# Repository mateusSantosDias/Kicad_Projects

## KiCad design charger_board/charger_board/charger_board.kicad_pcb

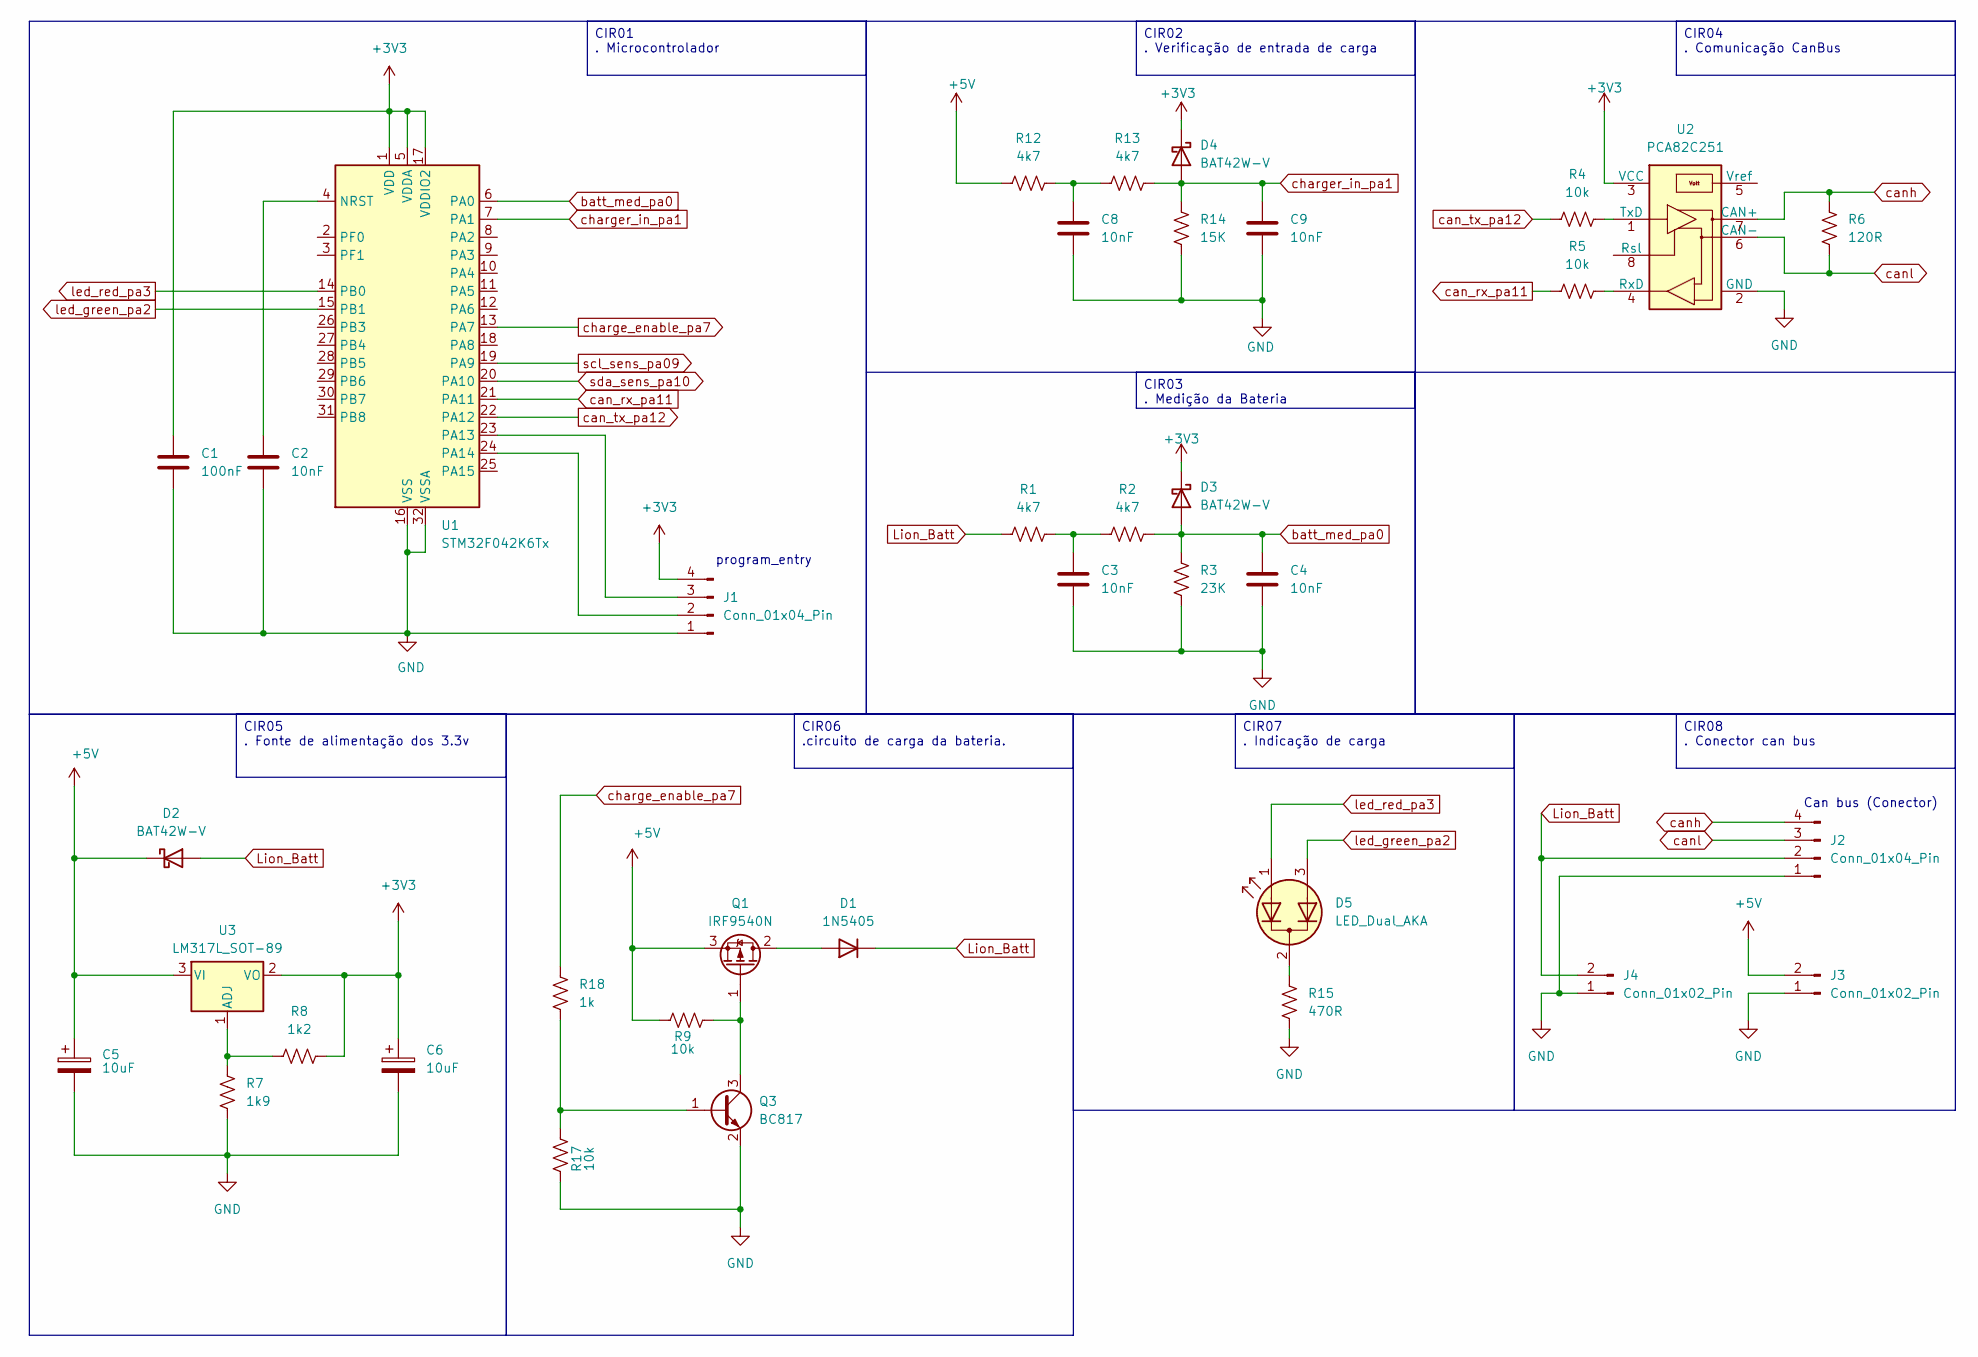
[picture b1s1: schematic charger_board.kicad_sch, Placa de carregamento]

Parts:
C1: 100nF; C_1206_3216Metric
C2, C3, C4, C8, C9: 10nF; C_1206_3216Metric
C5, C6: 10uF; C_Elec_5x5.4
D1: 1N5405; D_1206_3216Metric
D2, D3, D4: BAT42W-V; D_SOD-123
D5: LED_Dual_AKA; LED_D3.0mm-3
J1, J2: Conn_01x04_Pin; PinHeader_1x04_P2.54mm_Vertical
J3, J4: Conn_01x02_Pin; PinHeader_1x02_P2.54mm_Vertical
Q1: IRF9540N; TO-252-2
Q3: BC817; SOT-23
R1, R2, R12, R13: 4k7; R_1206_3216Metric
R3: 23K; R_1206_3216Metric
R4, R5, R9, R17: 10k; R_1206_3216Metric
R6: 120R; R_1206_3216Metric
R7: 1k9; R_1206_3216Metric
R8: 1k2; R_1206_3216Metric
R14: 15K; R_1206_3216Metric
R15: 470R; R_1206_3216Metric
R18: 1k; R_1206_3216Metric
U1: STM32F042K6Tx; LQFP-32_7x7mm_P0.8mm
U2: PCA82C251; SO-8_3.9x4.9mm_P1.27mm
U3: LM317L_SOT-89; SOT-89-3

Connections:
+3V3: C1.1, C6.1, D3.1 (K), D4.1 (K), J1.4, R8.2, U1.1 (VDD), U1.5 (VDDA), U1.17 (VDDIO2), U2.3 (VCC), U3.2 (VO)
+5V: C5.1, D2.1 (K), J3.2, Q1.3 (S), R9.2, R12.1, U3.3 (VI)
GND: C1.2, C2.2, C3.2, C4.2, C5.2, C6.2, C8.2, C9.2, J1.1, J2.1, J3.1, J4.1, Q3.2 (E), R3.1, R7.1, R14.1, R15.1, R17.2, U1.16 (VSS), U1.32 (VSSA), U2.2 (GND)
Lion_Batt: D1.1 (K), D2.2 (A), J2.2, J4.2, R1.1
unnamed: C3.1, R1.2, R2.1
unnamed: C8.1, R12.2, R13.1
unnamed: D1.2 (A), Q1.2 (D)
unnamed: D5.2 (K), R15.2
unnamed: J1.2, U1.24 (PA14)
unnamed: J1.3, U1.23 (PA13)
unnamed: Q1.1 (G), Q3.3 (C), R9.1
unnamed: Q3.1 (B), R17.1, R18.2
unnamed: C2.1, U1.4 (NRST)
unnamed: R5.2, U2.4 (RxD)
unnamed: R4.2, U2.1 (TxD)
unnamed: R7.2, R8.1, U3.1 (ADJ)
batt_med_pa0: C4.1, D3.2 (A), R2.2, R3.2, U1.6 (PA0)
can_rx_pa11: R5.1, U1.21 (PA11)
can_tx_pa12: R4.1, U1.22 (PA12)
canh: J2.4, R6.2, U2.7 (CAN+)
canl: J2.3, R6.1, U2.6 (CAN-)
charge_enable_pa7: R18.1, U1.13 (PA7)
charger_in_pa1: C9.1, D4.2 (A), R13.2, R14.2, U1.7 (PA1)
led_green_pa2: D5.3 (A2), U1.15 (PB1)
led_red_pa3: D5.1 (A1), U1.14 (PB0)
scl_sens_pa09: U1.19 (PA9)
sda_sens_pa10: U1.20 (PA10)

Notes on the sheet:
Can bus (Conector)
program_entry
CIR06 .circuito de carga da bateria.
CIR07 . Indicação de carga
CIR08 . Conector can bus
CIR05 . Fonte de alimentação dos 3.3v
CIR04 . Comunicação CanBus
CIR02 . Verificação de entrada de carga
CIR01 . Microcontrolador
CIR03 . Medição da Bateria

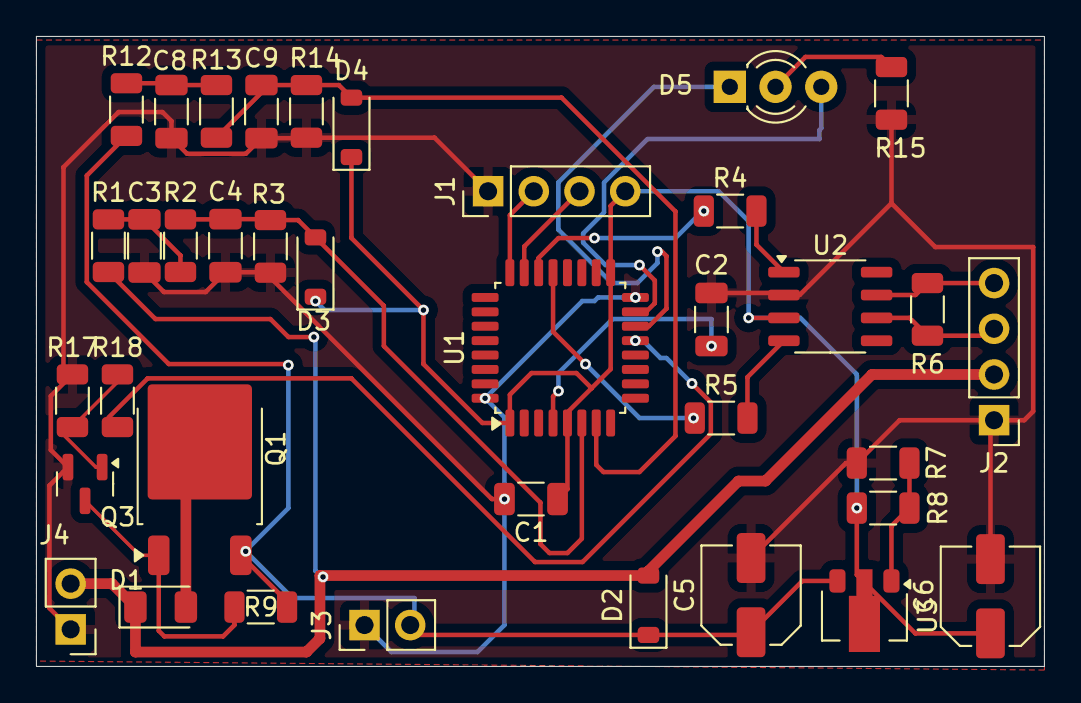
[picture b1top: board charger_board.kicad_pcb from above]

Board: 2 copper layers, 56.0 x 35.0 mm, 37 parts (0 on the bottom side), 25 nets.

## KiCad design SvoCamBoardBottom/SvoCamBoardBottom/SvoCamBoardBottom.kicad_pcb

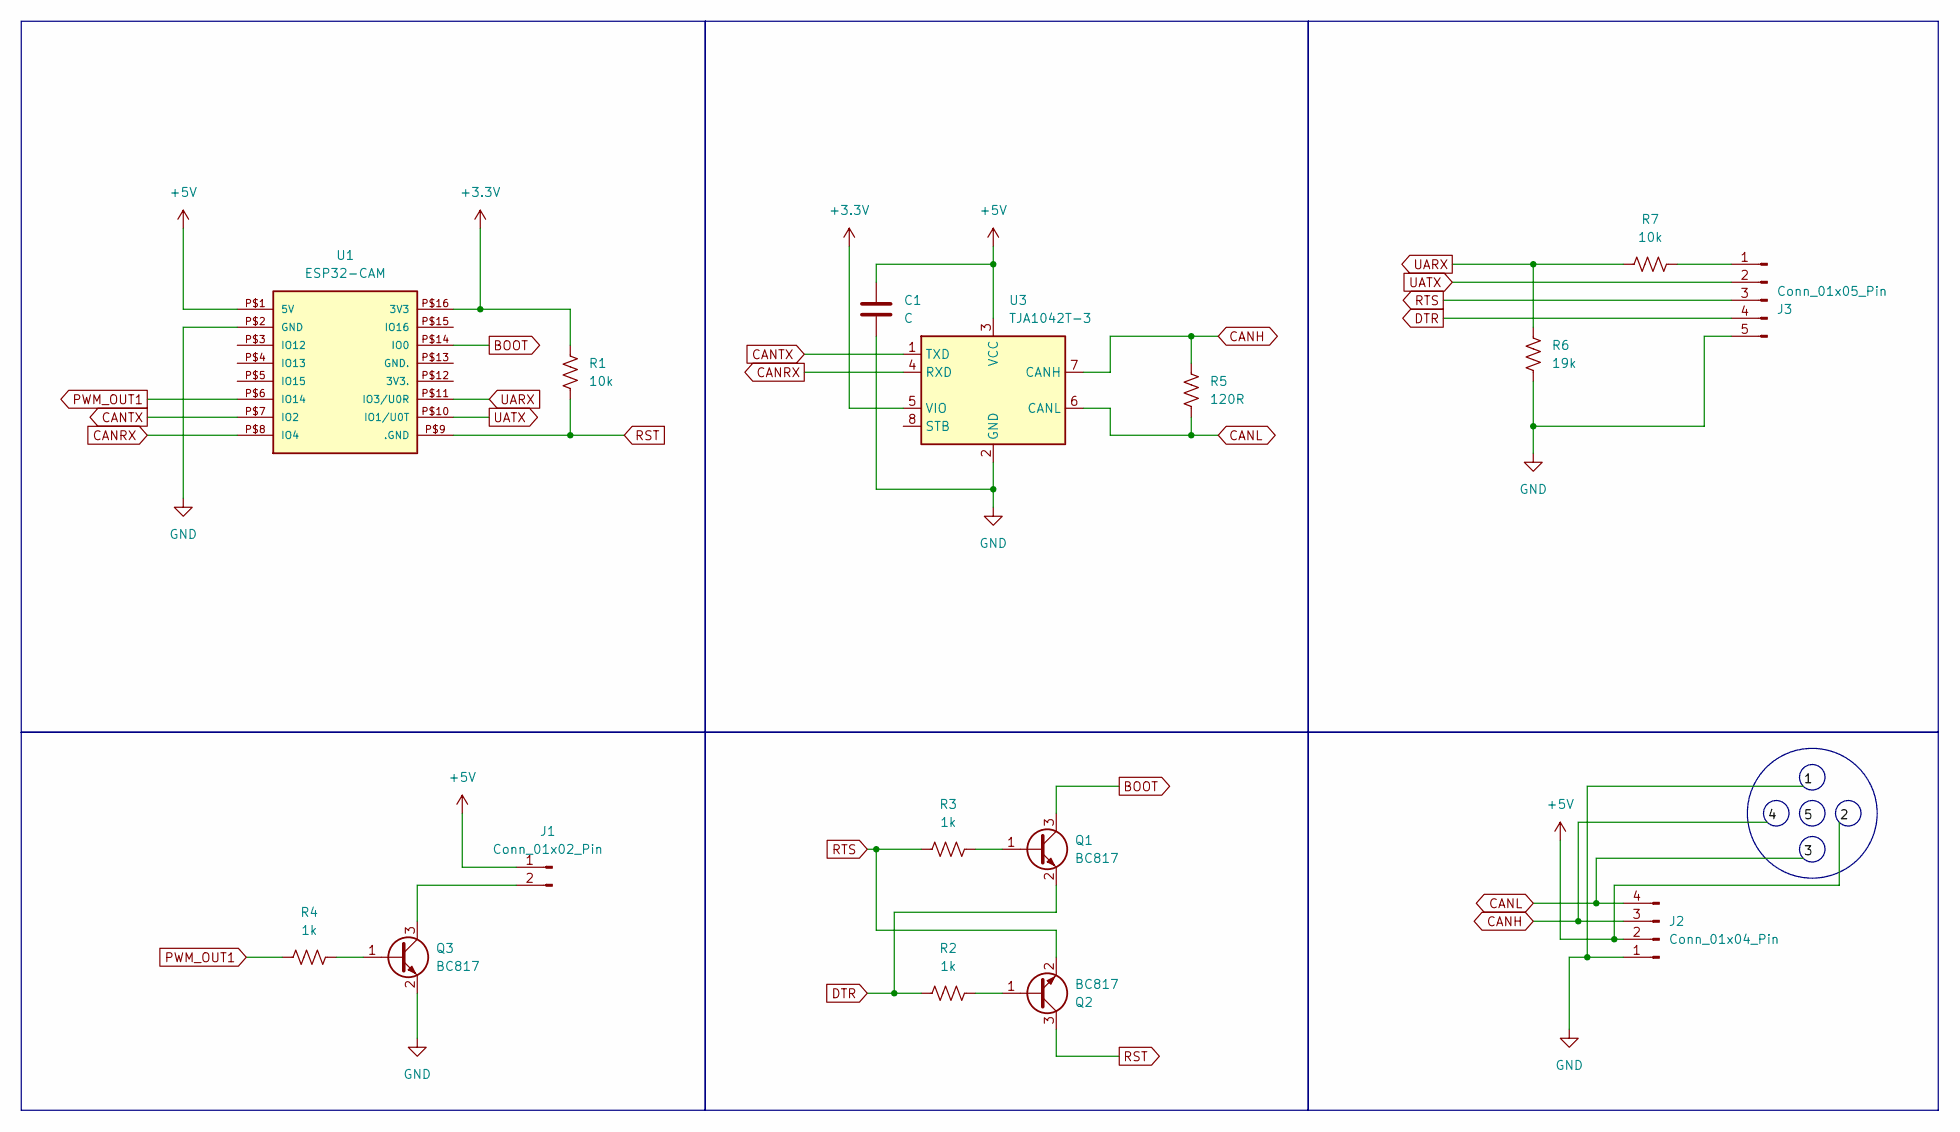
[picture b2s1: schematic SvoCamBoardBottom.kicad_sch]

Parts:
C1: C; C_1206_3216Metric
J1: Conn_01x02_Pin; PinHeader_1x02_P2.54mm_Vertical
J2: Conn_01x04_Pin; PinHeader_1x04_P2.54mm_Vertical
J3: Conn_01x05_Pin; PinHeader_1x05_P2.54mm_Vertical
Q1, Q2, Q3: BC817; SOT-23
R1, R7: 10k; R_0805_2012Metric
R2, R3, R4: 1k; R_0805_2012Metric
R5: 120R; R_0805_2012Metric
R6: 19k; R_0805_2012Metric
U1: ESP32-CAM
U3: TJA1042T-3; SOIC-8_3.9x4.9mm_P1.27mm

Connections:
+3.3V: R1.1, U1.P$16 (3V3), U3.5 (VIO)
+5V: C1.1, J1.1, J2.2, U1.P$1 (5V), U3.3 (VCC)
BOOT: Q1.3 (C), U1.P$14 (IO0)
CANH: J2.3, R5.1, U3.7 (CANH)
CANL: J2.4, R5.2, U3.6 (CANL)
CANRX: U1.P$8 (IO4), U3.4 (RXD)
CANTX: U1.P$7 (IO2), U3.1 (TXD)
DTR: J3.4, Q1.2 (E), R2.1
GND: C1.2, J2.1, J3.5, Q3.2 (E), R6.2, U1.P$2 (GND), U3.2 (GND)
unnamed: J1.2, Q3.3 (C)
unnamed: J3.1, R7.2
unnamed: Q1.1 (B), R3.2
unnamed: Q2.1 (B), R2.2
unnamed: Q3.1 (B), R4.2
PWM_OUT1: R4.1, U1.P$6 (IO14)
RST: Q2.3 (C), R1.2, U1.P$9 (.GND)
RTS: J3.3, Q2.2 (E), R3.1
UARX: R6.1, R7.1, U1.P$11 (IO3/U0R)
UATX: J3.2, U1.P$10 (IO1/U0T)

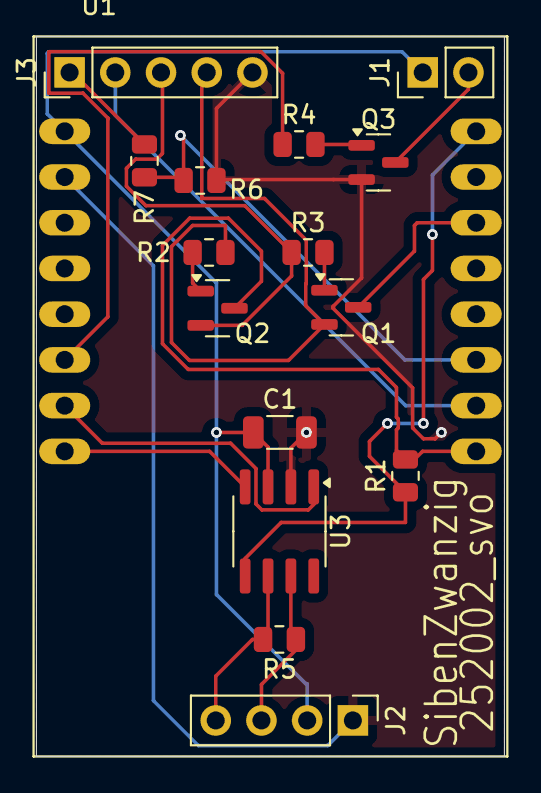
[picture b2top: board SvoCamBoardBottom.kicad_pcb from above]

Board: 2 copper layers, 26.0 x 40.0 mm, 16 parts (0 on the bottom side), 19 nets.

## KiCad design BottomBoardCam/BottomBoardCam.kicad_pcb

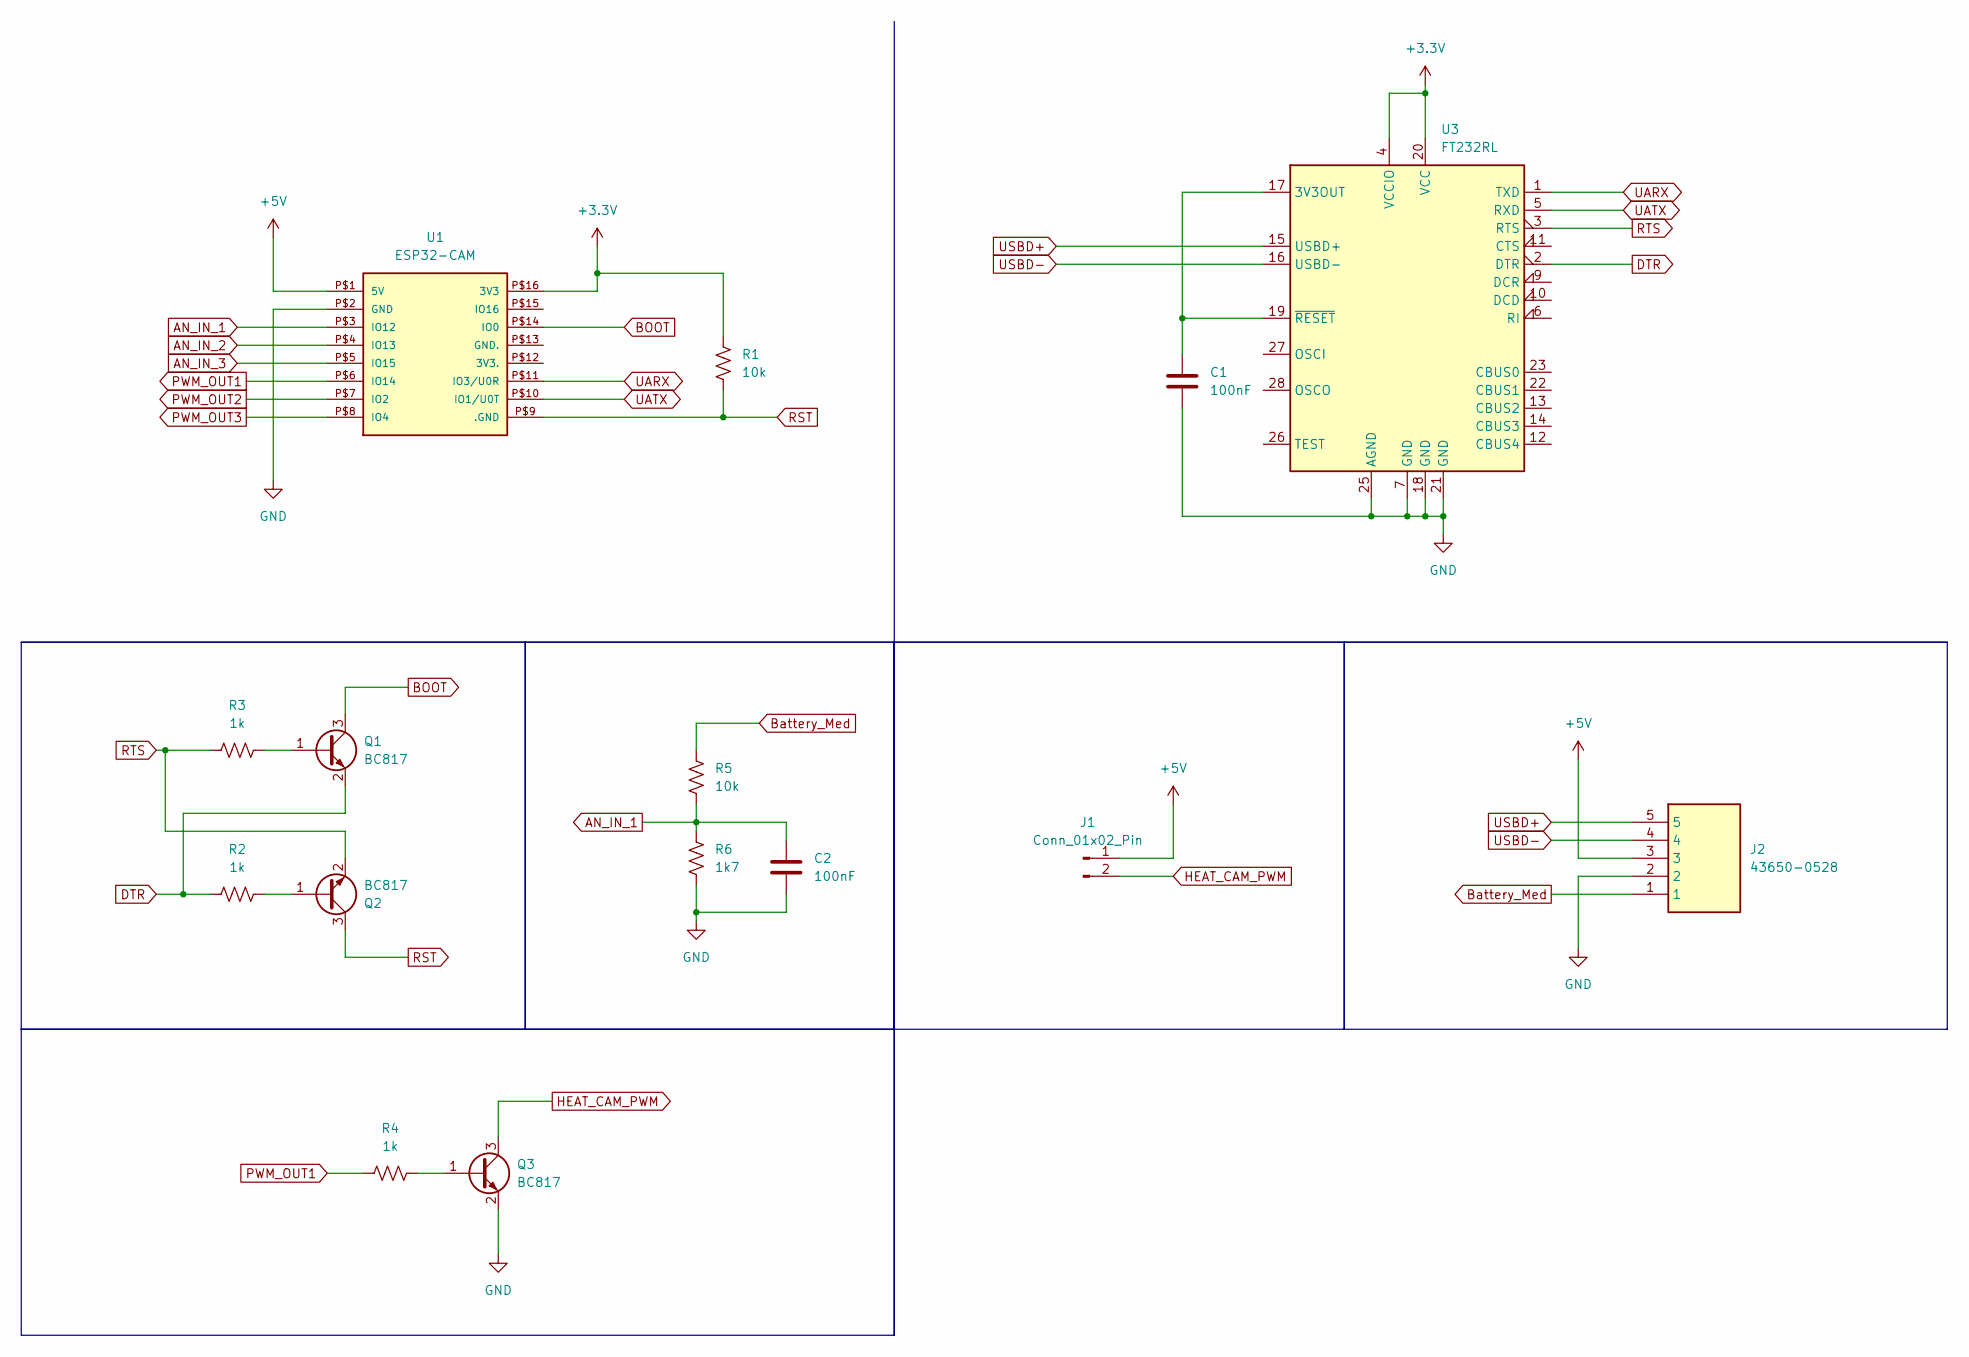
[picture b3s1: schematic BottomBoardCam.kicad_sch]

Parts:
C1: 100nF; C_01005_0402Metric
C2: 100nF; C_0805_2012Metric
J1: Conn_01x02_Pin; PinHeader_1x02_P2.54mm_Vertical
J2: 43650-0528; 43650-05YY_272829; Mouser Part Number 538-43650-0528
Q1, Q2, Q3: BC817; SOT-23
R1, R5: 10k; R_0805_2012Metric
R2, R3, R4: 1k; R_0805_2012Metric
R6: 1k7; R_0805_2012Metric
U1: ESP32-CAM
U3: FT232RL; SSOP-28_5.3x10.2mm_P0.65mm

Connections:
+3.3V: R1.1, U1.P$16 (3V3), U3.4 (VCCIO), U3.20 (VCC)
+5V: J1.1, J2.3, U1.P$1 (5V)
AN_IN_1: C2.1, R5.2, R6.2, U1.P$3 (IO12)
AN_IN_2: U1.P$4 (IO13)
AN_IN_3: U1.P$5 (IO15)
BOOT: Q1.3 (C), U1.P$14 (IO0)
Battery_Med: J2.1, R5.1
DTR: Q1.2 (E), R2.1, U3.2 (DTR)
GND: C1.2, C2.2, J2.2, Q3.2 (E), R6.1, U1.P$2 (GND), U3.7 (GND), U3.18 (GND), U3.21 (GND), U3.25 (AGND)
HEAT_CAM_PWM: J1.2, Q3.3 (C)
unnamed: Q1.1 (B), R3.2
unnamed: Q2.1 (B), R2.2
unnamed: Q3.1 (B), R4.2
unnamed: C1.1, U3.17 (3V3OUT), U3.19 (~RESET)
PWM_OUT1: R4.1, U1.P$6 (IO14)
PWM_OUT2: U1.P$7 (IO2)
PWM_OUT3: U1.P$8 (IO4)
RST: Q2.3 (C), R1.2, U1.P$9 (.GND)
RTS: Q2.2 (E), R3.1, U3.3 (RTS)
UARX: U1.P$11 (IO3/U0R), U3.1 (TXD)
UATX: U1.P$10 (IO1/U0T), U3.5 (RXD)
USBD+: J2.5, U3.15 (USBD+)
USBD-: J2.4, U3.16 (USBD-)

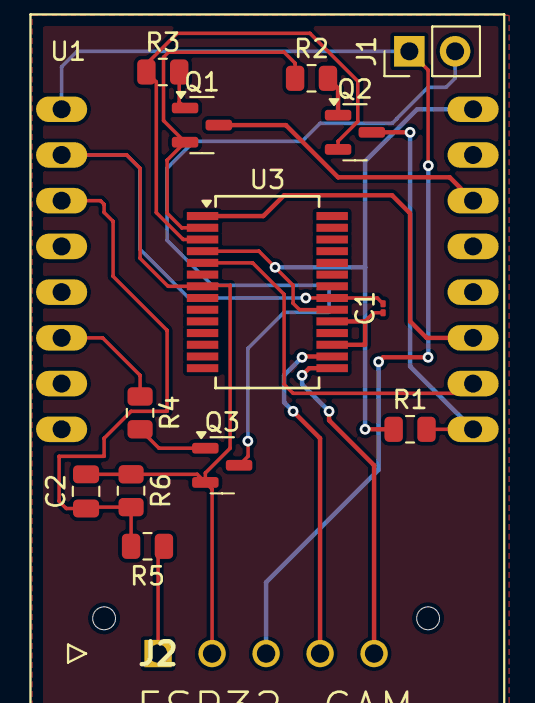
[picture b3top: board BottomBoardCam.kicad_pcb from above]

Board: 2 copper layers, 15 parts (0 on the bottom side), 19 nets.

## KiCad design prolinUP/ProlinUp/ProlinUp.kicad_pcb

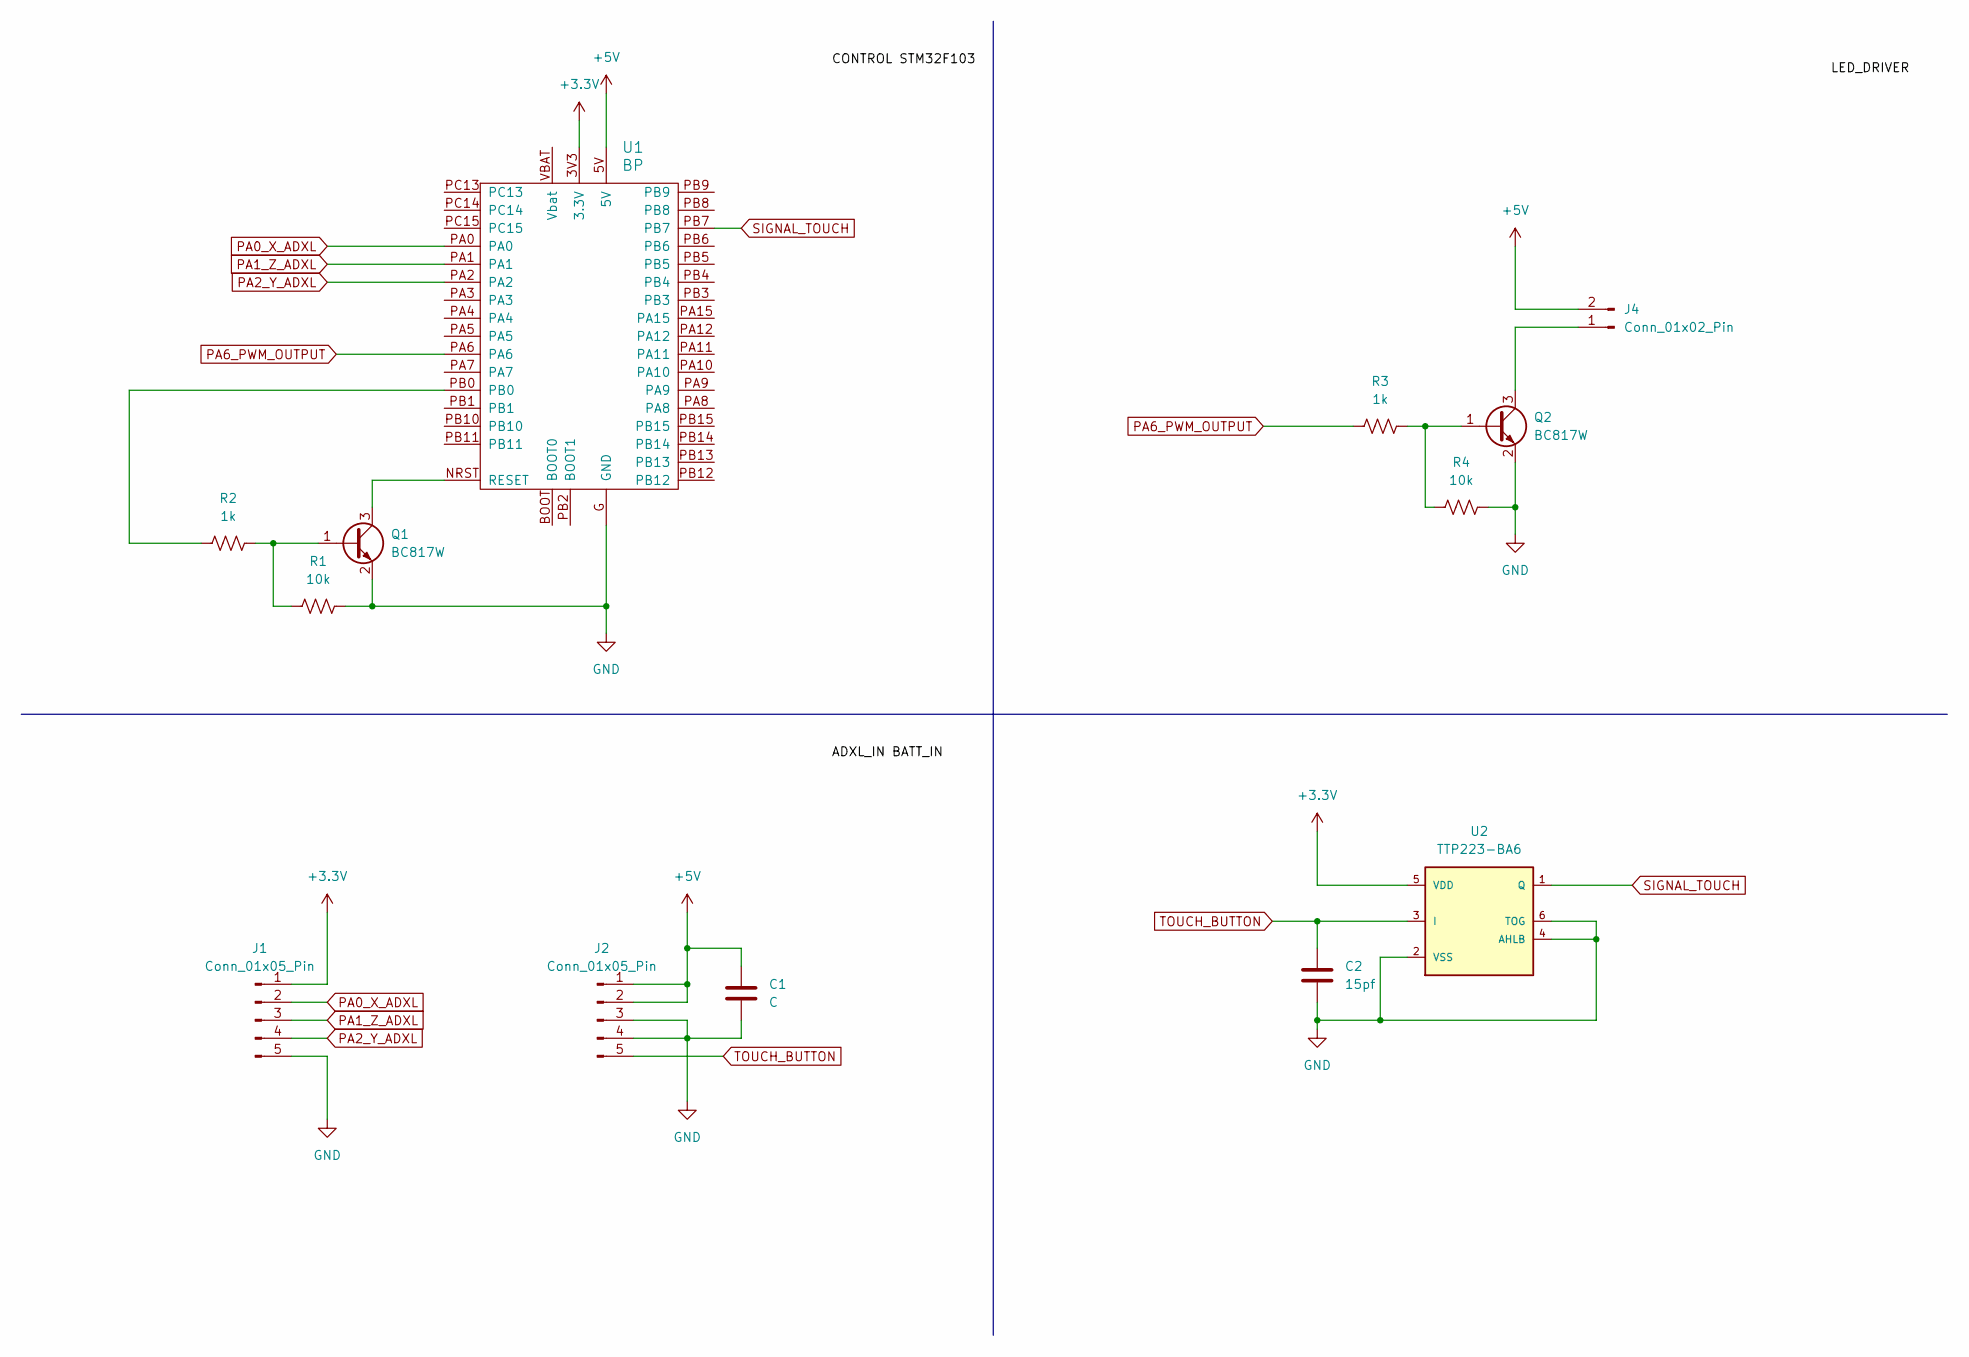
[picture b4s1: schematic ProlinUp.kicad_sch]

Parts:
C1: C; C_1206_3216Metric
C2: 15pf; C_1206_3216Metric
J1: Conn_01x05_Pin; PinHeader_1x05_P2.54mm_Vertical
J2: Conn_01x05_Pin; PinHeader_1x05_P2.54mm_Horizontal
J4: Conn_01x02_Pin; PinHeader_1x02_P2.54mm_Vertical
Q1, Q2: BC817W; SOT-323_SC-70
R1, R4: 10k; R_1206_3216Metric
R2, R3: 1k; R_1206_3216Metric
U1: BP; blue_pill
U2: TTP223-BA6; SOT23-6

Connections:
+3.3V: J1.1, U1.3V3 (3.3V), U2.5 (VDD)
+5V: C1.1, J2.1, J2.2, J4.2, U1.5V
GND: C1.2, C2.2, J1.5, J2.3, J2.4, Q1.2 (E), Q2.2 (E), R1.2, R4.2, U1.G (GND), U2.2 (VSS), U2.4 (AHLB), U2.6 (TOG)
unnamed: J4.1, Q2.3 (C)
unnamed: Q1.1 (B), R1.1, R2.2
unnamed: Q1.3 (C), U1.NRST (RESET)
unnamed: Q2.1 (B), R3.2, R4.1
unnamed: R2.1, U1.PB0
PA0_X_ADXL: J1.2, U1.PA0
PA1_Z_ADXL: J1.3, U1.PA1
PA2_Y_ADXL: J1.4, U1.PA2
PA6_PWM_OUTPUT: R3.1, U1.PA6
SIGNAL_TOUCH: U1.PB7, U2.1 (Q)
TOUCH_BUTTON: C2.1, J2.5, U2.3 (I)

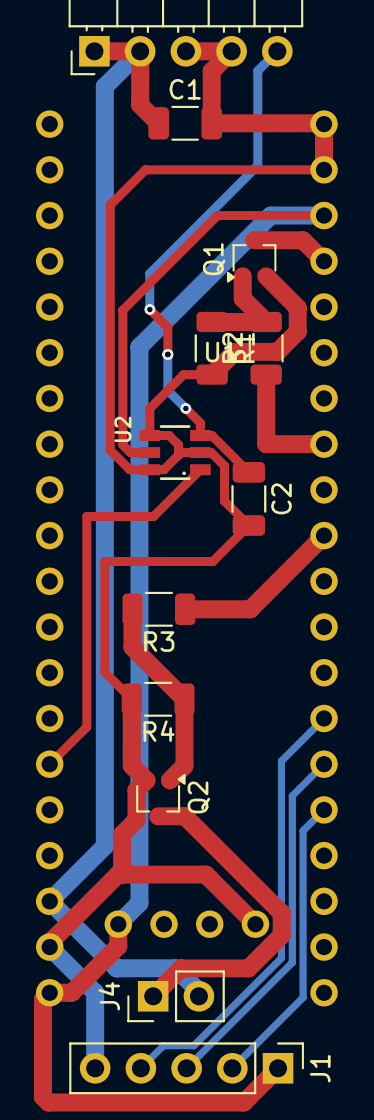
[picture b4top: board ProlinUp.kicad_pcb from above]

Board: 2 copper layers, 13 parts (0 on the bottom side), 14 nets.

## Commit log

2025-07-09 KicadProjects
2025-08-25 impl
2025-08-29 svocanboard
2025-09-07 svocamboard
2025-11-10 placa bms pronta
